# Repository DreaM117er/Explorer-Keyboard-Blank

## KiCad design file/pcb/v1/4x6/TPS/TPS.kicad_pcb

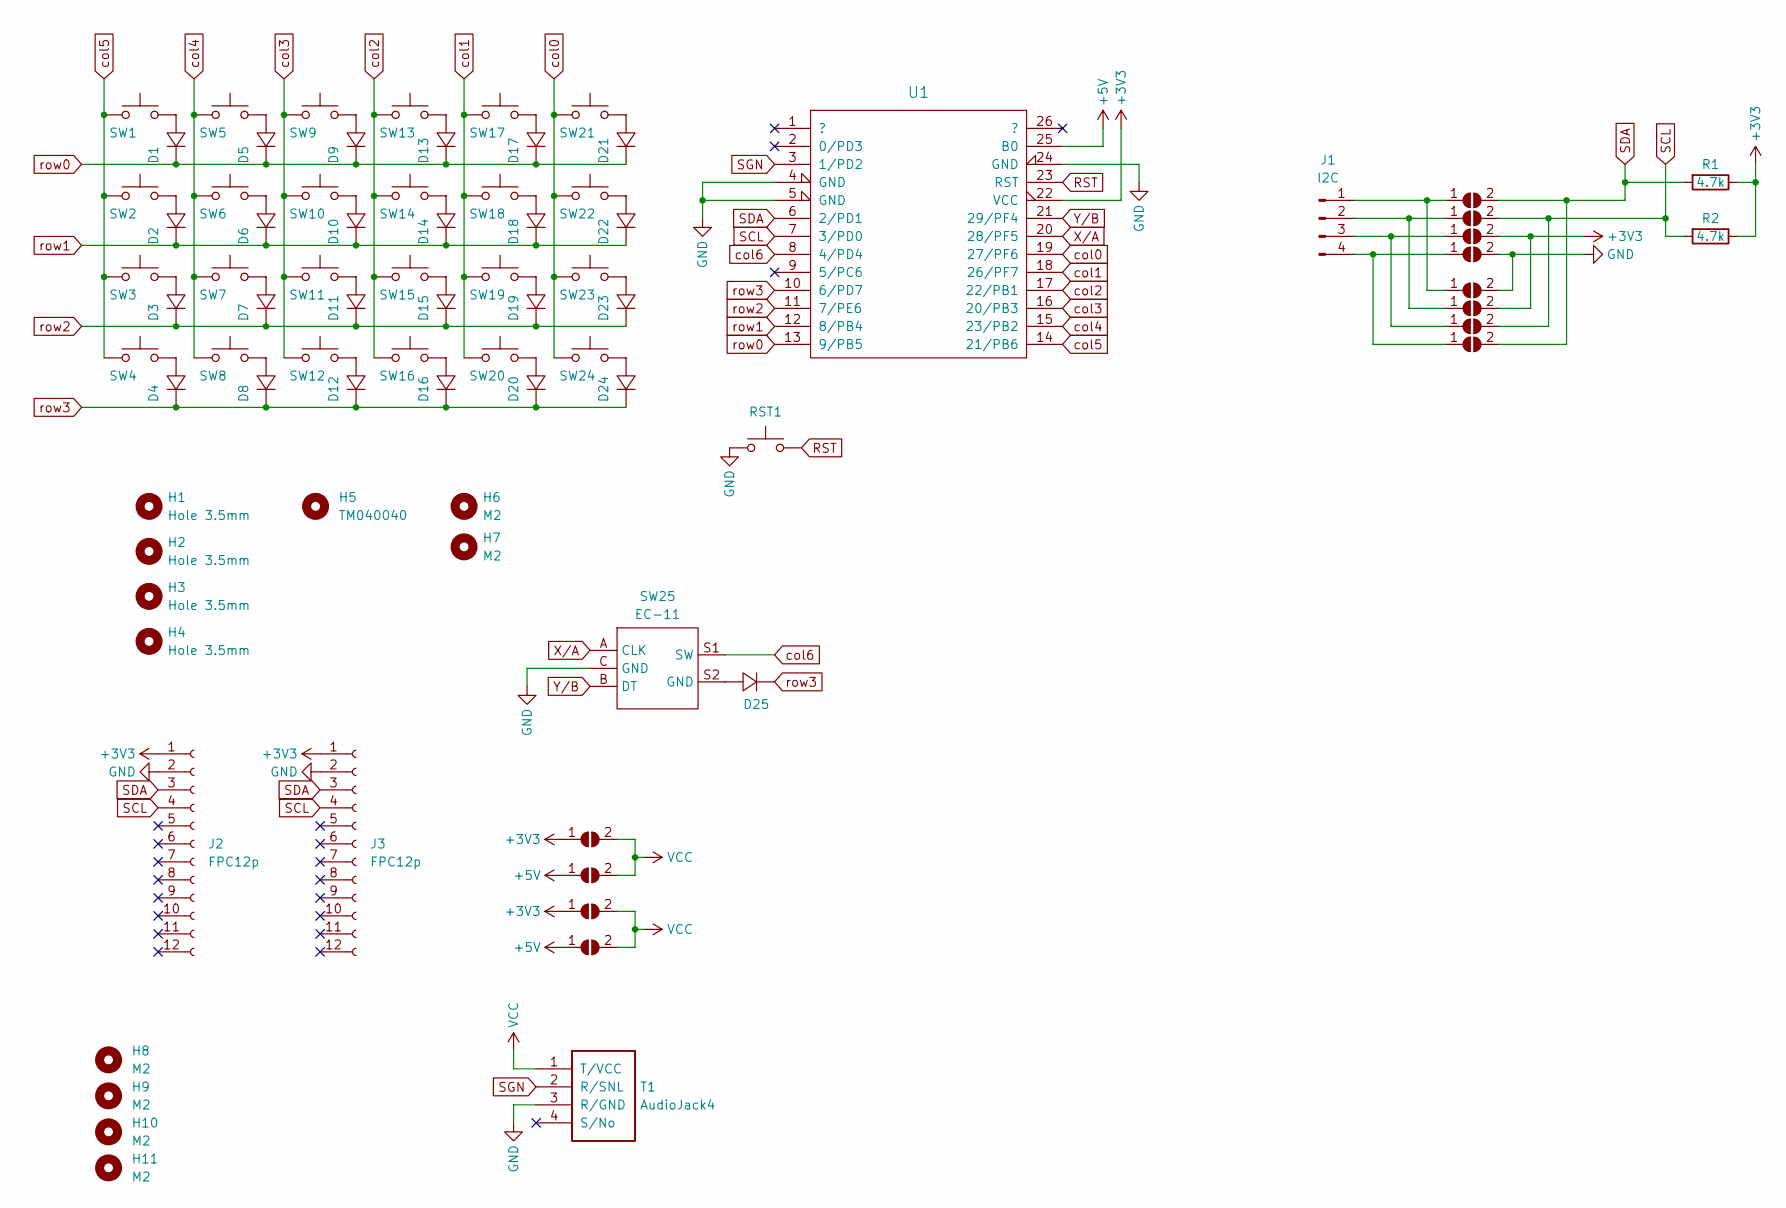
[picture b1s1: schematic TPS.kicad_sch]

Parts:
D1, D2, D3, D4, D5, D6, D7, D8, D9, D10, D11, D12, D13, D14, D15, D16, D17, D18, D19, D20, D21, D22, D23, D24, D25: 1N4148_SMD; D_SOD-123_dual
H1, H2, H3, H4: Hole 3.5mm; MountingHole_3.5mm
H5: TM040040; Trackpad_Cirque_TM040040
H6, H7, H8, H9, H10, H11: M2; MountingHole_2.2mm_M2
J1: I2C; PinHeader_1x04_P2.54mm_Vertical
J2, J3: FPC12p; Hirose_FH12-12S-0.5SH_1x12-1MP_P0.50mm_Horizontal
JP1, JP2, JP3, JP4: PWR1; SolderJumper-2_P1.3mm_Open_Pad1.0x1.5mm
JP5, JP6, JP7, JP8, JP9, JP10, JP11, JP12: PWR1; SolderJumper-2_P1.3mm_Open_RoundedPad1.0x1.5mm
R1, R2: 4.7k; R_Axial_DIN0204_L3.6mm_D1.6mm_P7.62mm_Horizontal
RST1: SW_Push; ResetSW_1side
SW1, SW2, SW3, SW4, SW5, SW6, SW7, SW8, SW9, SW10, SW11, SW12, SW13, SW14, SW15, SW16, SW17, SW18, SW19, SW20, SW21, SW22, SW23, SW24: SW_Push; SW_Choc_GLP_KLP12_Hotswap_1.00u_dual
SW25: EC-11; RotaryEncoder_EC11
T1: AudioJack4; TRRS-PJ-320A, dual side x2
U1: MCU_ProMicro_13p; MCU_ProMicro_13p_dual

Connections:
+3V3: J2.1, J3.1, JP1.1 (A), JP3.1 (A), JP7.2 (B), JP10.2 (B), R1.1, R2.1, U1.22 (VCC)
+5V: JP2.1 (A), JP4.1 (A), U1.25 (B0)
GND: J2.2, J3.2, JP8.2 (B), JP9.2 (B), RST1.1, SW25.C (GND), T1.3 (R/GND), U1.4 (GND), U1.5 (GND), U1.24 (GND)
unnamed: D1.2, SW1.2
unnamed: D2.2, SW2.2
unnamed: D3.2, SW3.2
unnamed: D4.2, SW4.2
unnamed: D5.2, SW5.2
unnamed: D6.2, SW6.2
unnamed: D7.2, SW7.2
unnamed: D8.2, SW8.2
unnamed: D9.2, SW9.2
unnamed: D10.2, SW10.2
unnamed: D11.2, SW11.2
unnamed: D12.2, SW12.2
unnamed: D13.2, SW13.2
unnamed: D14.2, SW14.2
unnamed: D15.2, SW15.2
unnamed: D16.2, SW16.2
unnamed: D17.2, SW17.2
unnamed: D18.2, SW18.2
unnamed: D19.2, SW19.2
unnamed: D20.2, SW20.2
unnamed: D21.2, SW21.2
unnamed: D22.2, SW22.2
unnamed: D23.2, SW23.2
unnamed: D24.2, SW24.2
unnamed: D25.2, SW25.S2 (GND)
unnamed: J1.1, JP5.1 (A), JP9.1 (A)
unnamed: J1.2, JP6.1 (A), JP10.1 (A)
unnamed: J1.3, JP7.1 (A), JP11.1 (A)
unnamed: J1.4, JP8.1 (A), JP12.1 (A)
RST: RST1.2, U1.23 (RST)
SCL: J2.4, J3.4, JP6.2 (B), JP11.2 (B), R2.2, U1.7 (3/PD0)
SDA: J2.3, J3.3, JP5.2 (B), JP12.2 (B), R1.2, U1.6 (2/PD1)
SGN: T1.2 (R/SNL), U1.3 (1/PD2)
VCC: JP1.2 (B), JP2.2 (B), JP3.2 (B), JP4.2 (B), T1.1 (T/VCC)
X/A: SW25.A (CLK), U1.20 (28/PF5)
Y/B: SW25.B (DT), U1.21 (29/PF4)
col0: SW21.1, SW22.1, SW23.1, SW24.1, U1.19 (27/PF6)
col1: SW17.1, SW18.1, SW19.1, SW20.1, U1.18 (26/PF7)
col2: SW13.1, SW14.1, SW15.1, SW16.1, U1.17 (22/PB1)
col3: SW9.1, SW10.1, SW11.1, SW12.1, U1.16 (20/PB3)
col4: SW5.1, SW6.1, SW7.1, SW8.1, U1.15 (23/PB2)
col5: SW1.1, SW2.1, SW3.1, SW4.1, U1.14 (21/PB6)
col6: SW25.S1 (SW), U1.8 (4/PD4)
row0: D1.1, D5.1, D9.1, D13.1, D17.1, D21.1, U1.13 (9/PB5)
row1: D2.1, D6.1, D10.1, D14.1, D18.1, D22.1, U1.12 (8/PB4)
row2: D3.1, D7.1, D11.1, D15.1, D19.1, D23.1, U1.11 (7/PE6)
row3: D4.1, D8.1, D12.1, D16.1, D20.1, D24.1, D25.1, U1.10 (6/PD7)

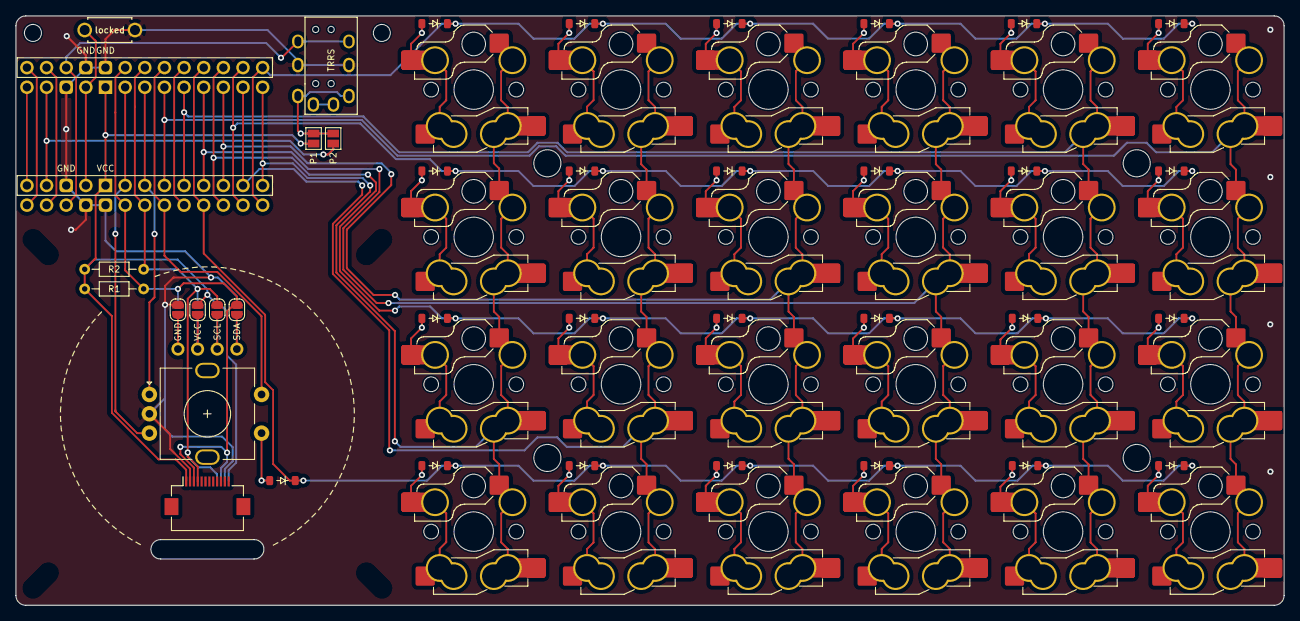
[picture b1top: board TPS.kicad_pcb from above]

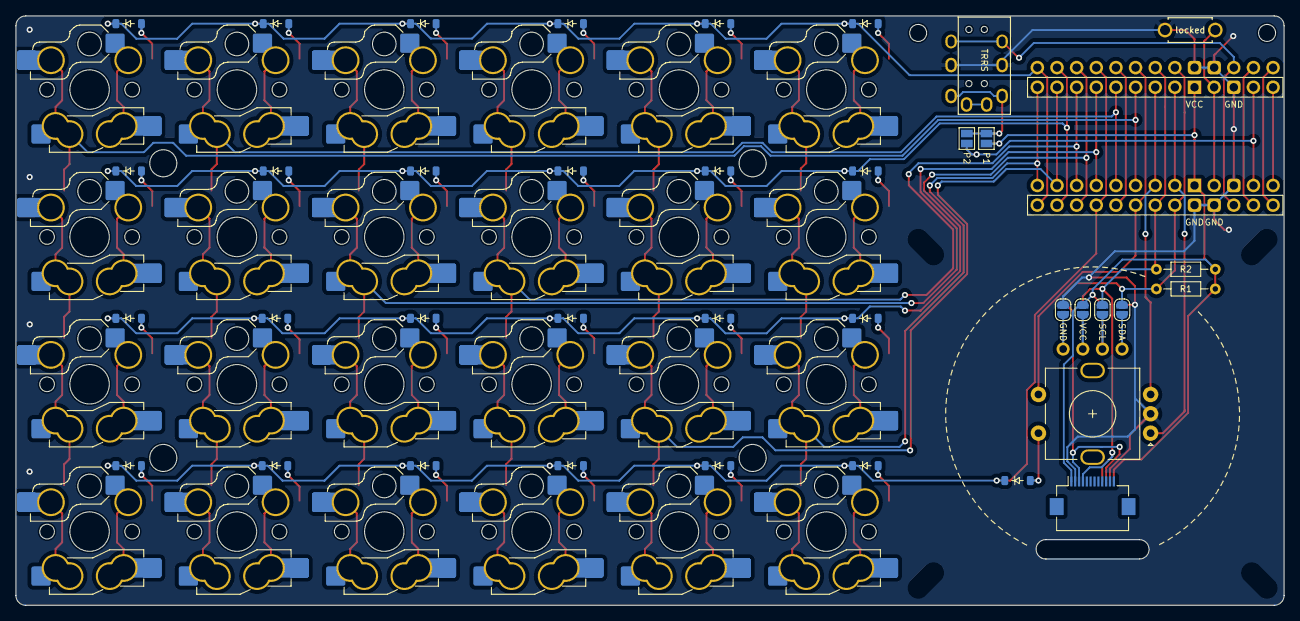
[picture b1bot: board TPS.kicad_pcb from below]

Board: 2 copper layers, 164.0 x 76.2 mm, 81 parts (8 on the bottom side), 50 nets.
